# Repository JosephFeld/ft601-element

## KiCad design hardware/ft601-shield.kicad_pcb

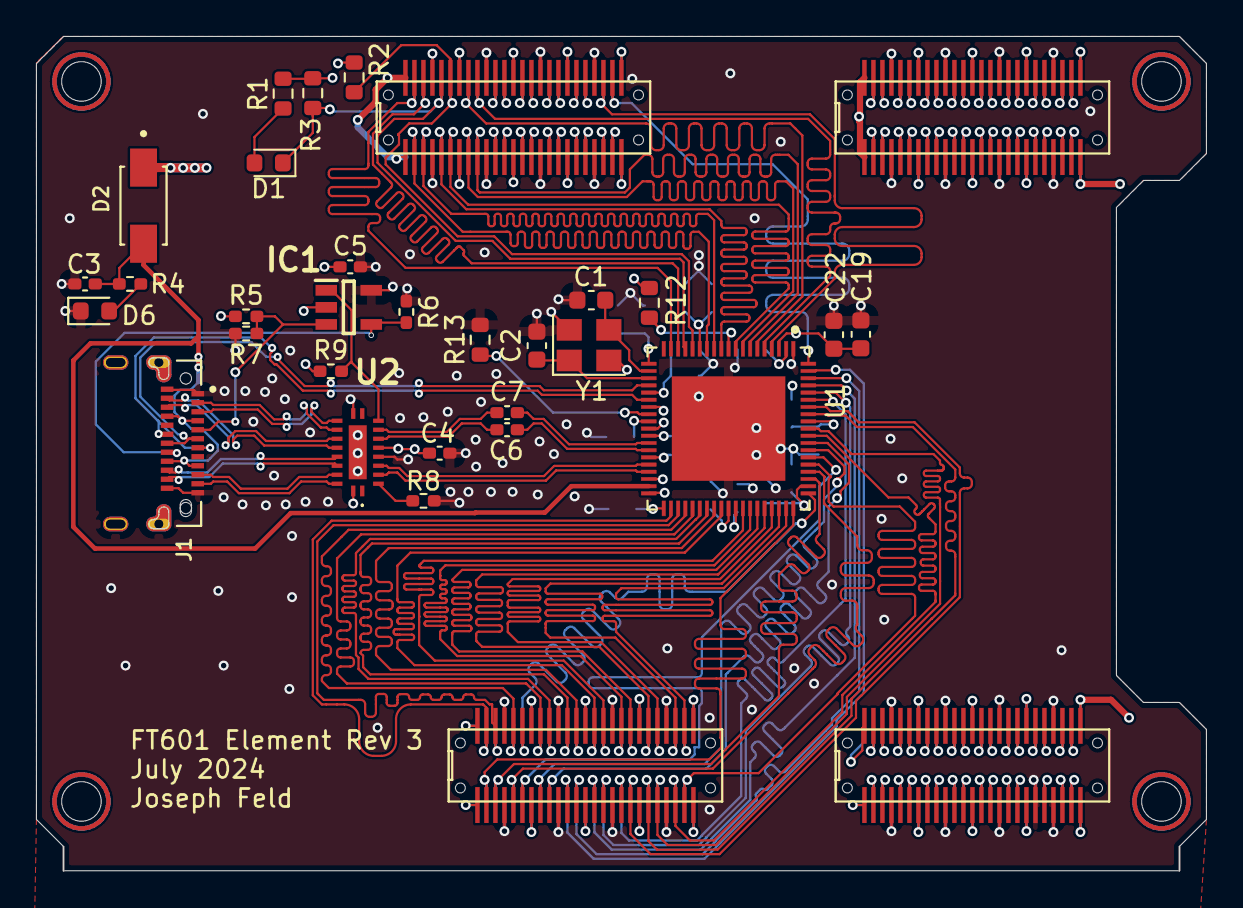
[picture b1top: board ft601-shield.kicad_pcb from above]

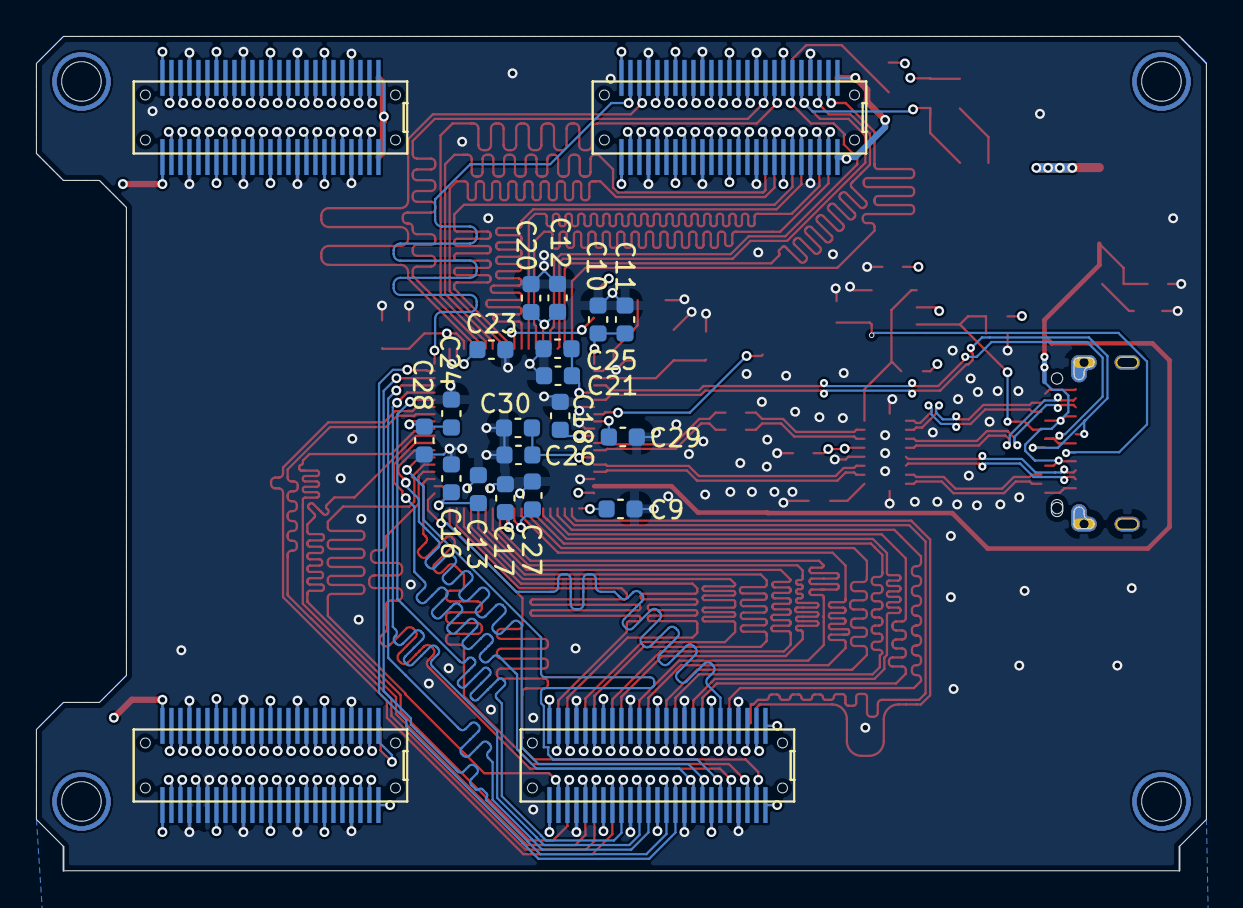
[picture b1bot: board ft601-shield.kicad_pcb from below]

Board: 4 copper layers, 65.0 x 46.4 mm, 47 parts (18 on the bottom side), 77 nets.

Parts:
B1: Alchitry_Element_AU; Element
C1, C2: 18p; C_0603_1608Metric
C3, C4, C5, C6, C7: 0.1u; C_0402_1005Metric_Pad0.74x0.62mm_HandSolder
C9: 10u; C_0603_1608Metric
C10, C12, C16, C17, C22, C23, C24, C25, C30: 100n; C_0603_1608Metric
C11, C13, C20, C21, C28, C29: 470n; C_0603_1608Metric
C18, C19, C26: 6.8n; C_0603_1608Metric
C27: 1u; C_0603_1608Metric
D1, D6: Green; LED_0603_1608Metric
D2: SK34A; DIOM4325X250N
IC1: MIC7221YM5-TR; SOT95P280X130-5N
J1: USB_C_Receptacle; AMPHENOL_12401899E412A
R1: 100; R_0603_1608Metric
R2, R3, R12: 10k; R_0603_1608Metric
R4: 4.3k; R_0402_1005Metric_Pad0.72x0.64mm_HandSolder
R5, R9: 100k; R_0402_1005Metric_Pad0.72x0.64mm_HandSolder
R6, R7: 5.1k; R_0402_1005Metric_Pad0.72x0.64mm_HandSolder
R8: 10k; R_0402_1005Metric_Pad0.72x0.64mm_HandSolder
R13: 1.6k; R_0603_1608Metric
U1: FT601Q-B-T; QFN40P900X900X100-77N
U2: HD3SS3212IRKSR; SN74HCS541RKSR
Y1: 30Meg; Crystal_SMD_3225-4Pin_3.2x2.5mm

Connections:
+1V0: C9.1, C18.1, C19.1, C22.1, C23.1, C26.1, C27.1, C30.1, U1.2 (AVDD), U1.3 (VD10), U1.30 (VD10__1), U1.33 (VD10__2), U1.39 (DV10), U1.48 (VD10__3)
+3V3: B1.A_7 (3V3), B1.A_13 (3V3), B1.A_19 (3V3), B1.A_25 (3V3), B1.A_26 (3V3), B1.A_32 (3V3), B1.A_38 (3V3), B1.A_44 (3V3), B1.B_7 (3V3), B1.B_13 (3V3), B1.B_19 (3V3), B1.B_25 (3V3), B1.B_26 (3V3), B1.B_32 (3V3), B1.B_38 (3V3), B1.B_44 (3V3), B1.C_7 (3V3), B1.C_13 (3V3), B1.C_19 (3V3), B1.C_25 (3V3), B1.C_26 (3V3), B1.C_32 (3V3), B1.C_38 (3V3), B1.C_44 (3V3), B1.D_7 (3V3), B1.D_13 (3V3), B1.D_19 (3V3), B1.D_25 (3V3), B1.D_26 (3V3), B1.D_32 (3V3), B1.D_38 (3V3), B1.D_44 (3V3), C4.2, C5.1, C10.1, C11.1, C12.1, C13.1, C16.1, C17.1, C20.1, C21.1, C24.1, C25.1, C28.1, C29.1, IC1.2 (V+), R1.2, R2.1, R3.1, R5.1, R9.1, R12.1, U1.14 (VCCIO), U1.20 (VCC33), U1.24 (VCC33__1), U1.28 (VDDA), U1.38 (VCC33__2), U1.49 (VCCIO__1), U1.59 (VCCIO__2), U1.68 (VCCIO__3), U2.6 (VCC)
+5V: B1.A_1 (5V), B1.A_50 (5V), B1.B_1 (5V), B1.B_50 (5V), B1.C_1 (5V), B1.C_50 (5V), B1.D_1 (5V), B1.D_50 (5V), D2.C
/FT601/A0+: U1.35 (RIDP), U2.3 (A0P)
/FT601/A0-: U1.34 (RIDN), U2.4 (A0N)
/FT601/A1+: C6.1, U2.7 (A1P)
/FT601/A1-: C7.1, U2.8 (A1N)
/FT601/CC1: IC1.3 (IN+), J1.A5 (CC1), R5.2, R7.1
/FT601/CC2: IC1.4 (IN-), J1.B5 (CC2), R6.1
/FT601/D+: J1.A6 (D+), J1.B6 (D+), U1.23 (DP)
/FT601/D-: J1.A7 (D-), J1.B7 (D-), U1.25 (DM)
/FT601/RX1+: J1.B11 (RX1+), U2.15 (C0P)
/FT601/RX1-: J1.B10 (RX1-), U2.14 (C0N)
/FT601/RX2+: J1.A11 (RX2+), U2.19 (B0P)
/FT601/RX2-: J1.A10 (RX2-), U2.18 (B0N)
/FT601/SEL: IC1.1 (OUT), R9.2, U2.9 (SEL)
/FT601/TOD+: C6.2, U1.32 (T0DP)
/FT601/TOD-: C7.2, U1.31 (T0DN)
/FT601/TX1+: J1.A2 (TX1+), U2.13 (C1P)
/FT601/TX1-: J1.A3 (TX1-), U2.12 (C1N)
/FT601/TX2+: J1.B2 (TX2+), U2.17 (B1P)
/FT601/TX2-: J1.B3 (TX2-), U2.16 (B1N)
/FT601/VBUS: C3.1, D2.A, J1.A4 (VBUS), J1.A9 (VBUS), J1.B4 (VBUS), J1.B9 (VBUS), R4.2, U1.37 (VBUS)
BE_0: B1.A_28 (N6), U1.4 (BE_0)
BE_1: B1.A_42 (N9), U1.5 (BE_1)
BE_2: B1.A_43 (P9), U1.6 (BE_2)
BE_3: B1.A_9 (P8), U1.7 (BE_3)
CLK: B1.C_45 (N11), U1.58 (CLK)
DATA_0: B1.C_49 (P11), U1.40 (DATA_0)
DATA_1: B1.C_48 (P10), U1.41 (DATA_1)
DATA_2: B1.C_46 (N12), U1.42 (DATA_2)
DATA_3: B1.C_43 (P13), U1.43 (DATA_3)
DATA_4: B1.C_42 (N13), U1.44 (DATA_4)
DATA_5: B1.C_40 (M1), U1.45 (DATA_5)
DATA_6: B1.C_39 (M2), U1.46 (DATA_6)
DATA_7: B1.C_37 (P1), U1.47 (DATA_7)
DATA_8: B1.C_36 (N1), U1.50 (DATA_8)
DATA_9: B1.C_34 (R1), U1.51 (DATA_9)
DATA_10: B1.C_33 (R2), U1.52 (DATA_10)
DATA_11: B1.C_31 (T2), U1.53 (DATA_11)
DATA_12: B1.C_30 (R3), U1.54 (DATA_12)
DATA_13: B1.C_28 (T3), U1.55 (DATA_13)
DATA_14: B1.C_27 (T4), U1.56 (DATA_14)
DATA_15: B1.C_2 (T13), U1.57 (DATA_15)
DATA_16: B1.C_3 (R13), U1.60 (DATA_16)
DATA_17: B1.C_5 (T12), U1.61 (DATA_17)
DATA_18: B1.C_24 (P5), U1.62 (DATA_18)
DATA_19: B1.C_6 (R12), U1.63 (DATA_19)
DATA_20: B1.C_8 (R11), U1.64 (DATA_20)
DATA_21: B1.C_9 (R10), U1.65 (DATA_21)
DATA_22: B1.C_23 (L5), U1.66 (DATA_22)
DATA_23: B1.C_21 (M5), U1.67 (DATA_23)
DATA_24: B1.C_20 (N4), U1.69 (DATA_24)
DATA_25: B1.C_18 (L4), U1.70 (DATA_25)
DATA_26: B1.C_17 (M4), U1.71 (DATA_26)
DATA_27: B1.C_15 (P4), U1.72 (DATA_27)
DATA_28: B1.C_14 (P3), U1.73 (DATA_28)
DATA_29: B1.C_12 (N3), U1.74 (DATA_29)
DATA_30: B1.C_11 (N2), U1.75 (DATA_30)
DATA_31: B1.A_27 (M6), U1.76 (DATA_31)
GND: B1.A_4 (GND), B1.A_10 (GND), B1.A_16 (GND), B1.A_22 (GND), B1.A_29 (GND), B1.A_35 (GND), B1.A_41 (GND), B1.A_47 (GND), B1.B_4 (GND), B1.B_10 (GND), B1.B_16 (GND), B1.B_22 (GND), B1.B_29 (GND), B1.B_35 (GND), B1.B_41 (GND), B1.B_47 (GND), B1.C_4 (GND), B1.C_10 (GND), B1.C_16 (GND), B1.C_22 (GND), B1.C_29 (GND), B1.C_35 (GND), B1.C_41 (GND), B1.C_47 (GND), B1.D_4 (GND), B1.D_10 (GND), B1.D_16 (GND), B1.D_20 (VBSEL), B1.D_22 (GND), B1.D_29 (GND), B1.D_35 (GND), B1.D_41 (GND), B1.D_47 (GND), C1.2, C2.2, C3.2, C4.1, C5.2, C9.2, C10.2, C11.2, C12.2, C13.2, C16.2, C17.2, C18.2, C19.2, C20.2, C21.2, C22.2, C23.2, C24.2, C25.2, C26.2, C27.2, C28.2, C29.2, C30.2, D6.1 (K), IC1.5 (V-), J1.A1 (GND), J1.A12 (GND), J1.B1 (GND), J1.B12 (GND), J1.S1 (SHIELD), J1.S2 (SHIELD), J1.S3 (SHIELD), J1.S4 (SHIELD), R6.2, R7.2, R8.2, R13.1, U1.1 (GND), U1.26 (GND__1), U1.29 (GND__2), U1.36 (GND__3), U1.77 (EXP), U2.5 (GND), U2.11 (GND), U2.20 (GND), U2.21 (PAD), Y1.2, Y1.4
GPIO_0: B1.A_48 (T9), U1.17 (GPIO0)
GPIO_1: B1.A_49 (T10), U1.18 (GPIO1)
unnamed: D1.2 (A), R1.1
unnamed: D6.2 (A), R4.1
unnamed: R13.2, U1.27 (RREF)
unnamed: R12.2, U1.10 (SIWU_N)
unnamed: C1.1, U1.21 (XI), Y1.3
unnamed: C2.1, U1.22 (XO), Y1.1
unnamed: R8.1, U2.2 (OE_N)
OE_N: B1.A_2 (T8), U1.13 (OE_N)
RD_N: B1.A_3 (T7), U1.12 (RD_N)
RESET_N: B1.A_45 (R7), R2.2, U1.15 (RESET_N)
RXF_N: B1.A_6 (R5), U1.9 (RXF_N)
TXE_N: B1.A_8 (R8), U1.8 (TXE_N)
WAKEUP_N: B1.A_46 (R6), D1.1 (K), R3.2, U1.16 (WAKEUP_N)
WR_N: B1.A_5 (T5), U1.11 (WR_N)
